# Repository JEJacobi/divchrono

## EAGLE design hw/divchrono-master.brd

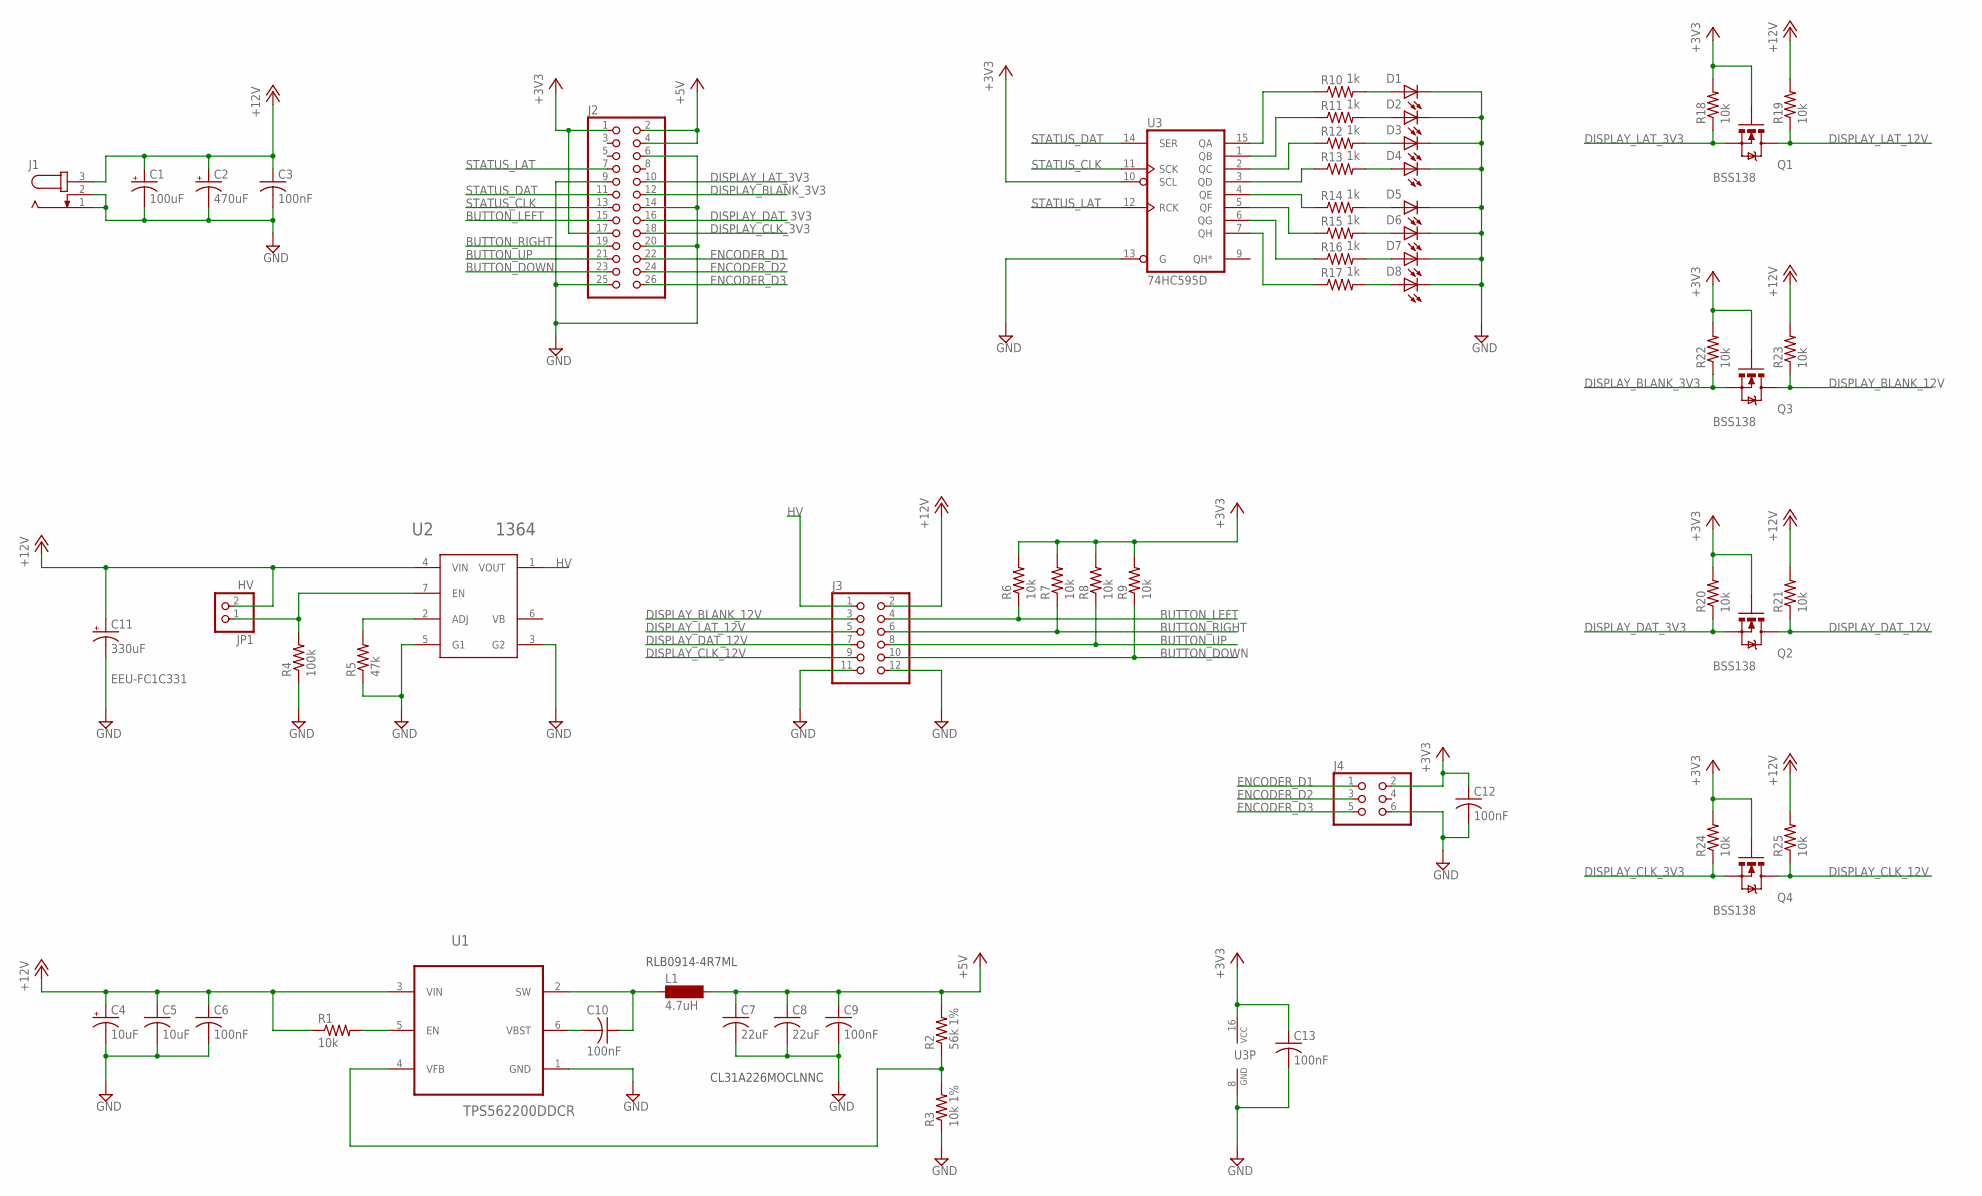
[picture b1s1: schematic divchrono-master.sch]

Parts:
C1: 100uF; E2,5-6
C2: 470uF; E2,5-6
C3, C6, C9, C10, C12, C13: 100nF; C1206
C4: 10uF; E2-5
C5: 10uF; C1206
C7, C8: 22uF; C1206
C11: 330uF; E3,5-8
D1, D2, D3, D4, D5, D6, D7, D8: LEDCHIPLED_1206; CHIPLED_1206
J1: JACK-PLUG0; SPC4077
J2: PINHD-2X13; 2X13
J3: PINHD-2X6; 2X06
J4: PINHD-2X3; 2X03
JP1: HV; 1X02
L1: 4.7uH; BS11
Q1, Q2, Q3, Q4: BSS138; SOT23-3
R1, R6, R7, R8, R9, R18, R19, R20, R21, R22, R23, R24, R25: 10k; R1206
R2: 56k 1%; R1206
R3: 10k 1%; R1206
R4: 100k; R1206
R5: 47k; R1206
R10, R11, R12, R13, R14, R15, R16, R17: 1k; R1206
U1: TPS562200DDCR; SOT95P280X110-6N
U2: 1364
U3: 74HC595D; SO16

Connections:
+3V3: C12.1, C13.1, J2.1, J2.17, J4.2, Q1.1 (G), Q2.1 (G), Q3.1 (G), Q4.1 (G), R6.2, R7.2, R8.2, R9.2, R18.2, R20.2, R22.2, R24.2, U3.10 (SCL), U3.16 (VCC)
+5V: C7.1, C8.1, C9.1, J2.2, J2.4, L1.2, R2.2
+12V: C1.+, C2.+, C3.1, C4.+, C5.1, C6.1, C11.+, J1.3, J3.2, JP1.2, R1.1, R19.2, R21.2, R23.2, R25.2, U1.3 (VIN), U2.4 (VIN)
BUTTON_DOWN: J2.23, J3.10, R9.1
BUTTON_LEFT: J2.15, J3.4, R6.1
BUTTON_RIGHT: J2.19, J3.6, R7.1
BUTTON_UP: J2.21, J3.8, R8.1
DISPLAY_BLANK_3V3: J2.12, Q3.2 (S), R22.1
DISPLAY_BLANK_12V: J3.3, Q3.3 (D), R23.1
DISPLAY_CLK_3V3: J2.18, Q4.2 (S), R24.1
DISPLAY_CLK_12V: J3.9, Q4.3 (D), R25.1
DISPLAY_DAT_3V3: J2.16, Q2.2 (S), R20.1
DISPLAY_DAT_12V: J3.7, Q2.3 (D), R21.1
DISPLAY_LAT_3V3: J2.10, Q1.2 (S), R18.1
DISPLAY_LAT_12V: J3.5, Q1.3 (D), R19.1
ENCODER_D1: J2.22, J4.1
ENCODER_D2: J2.24, J4.3
ENCODER_D3: J2.26, J4.5
GND: C1.-, C2.-, C3.2, C4.-, C5.2, C6.2, C7.2, C8.2, C9.2, C11.-, C12.2, C13.2, D1.C, D2.C, D3.C, D4.C, D5.C, D6.C, D7.C, D8.C, J1.1, J1.2, J2.6, J2.9, J2.14, J2.20, J2.25, J3.11, J3.12, J4.6, R3.1, R4.1, R5.1, U1.1 (GND), U2.3 (G2), U2.5 (G1), U3.8 (GND), U3.13 (G)
HV: J3.1, U2.1 (VOUT)
unnamed: R1.2, U1.5 (EN)
unnamed: C10.1, L1.1, U1.2 (SW)
unnamed: JP1.1, R4.2, U2.7 (EN)
unnamed: R5.2, U2.2 (ADJ)
unnamed: C10.2, U1.6 (VBST)
unnamed: R2.1, R3.2, U1.4 (VFB)
unnamed: R14.1, U3.4 (QE)
unnamed: R13.1, U3.3 (QD)
unnamed: R12.1, U3.2 (QC)
unnamed: D8.A, R17.2
unnamed: D7.A, R16.2
unnamed: D6.A, R15.2
unnamed: D5.A, R14.2
unnamed: R11.1, U3.1 (QB)
unnamed: R10.1, U3.15 (QA)
unnamed: R15.1, U3.5 (QF)
unnamed: R16.1, U3.6 (QG)
unnamed: R17.1, U3.7 (QH)
unnamed: D4.A, R13.2
unnamed: D3.A, R12.2
unnamed: D2.A, R11.2
unnamed: D1.A, R10.2
STATUS_CLK: J2.13, U3.11 (SCK)
STATUS_DAT: J2.11, U3.14 (SER)
STATUS_LAT: J2.7, U3.12 (RCK)

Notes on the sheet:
EEU-FC1C331
CL31A226MOCLNNC
RLB0914-4R7ML

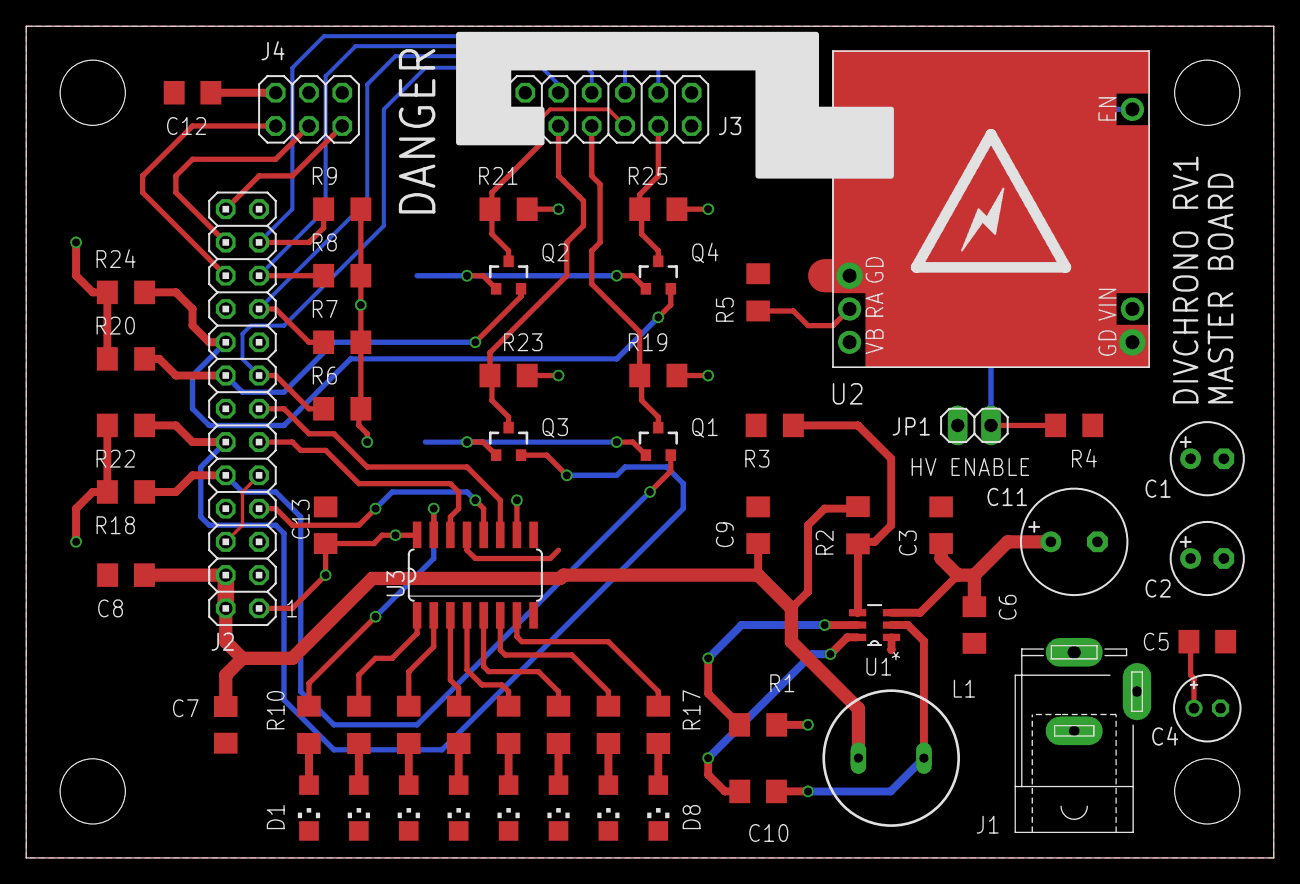
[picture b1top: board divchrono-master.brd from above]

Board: 2 copper layers, 95.2 x 63.5 mm, 61 parts (1 on the bottom side), 45 nets.

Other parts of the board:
U$1: ICON_DANGER
U$2: ICON_BOLT-L

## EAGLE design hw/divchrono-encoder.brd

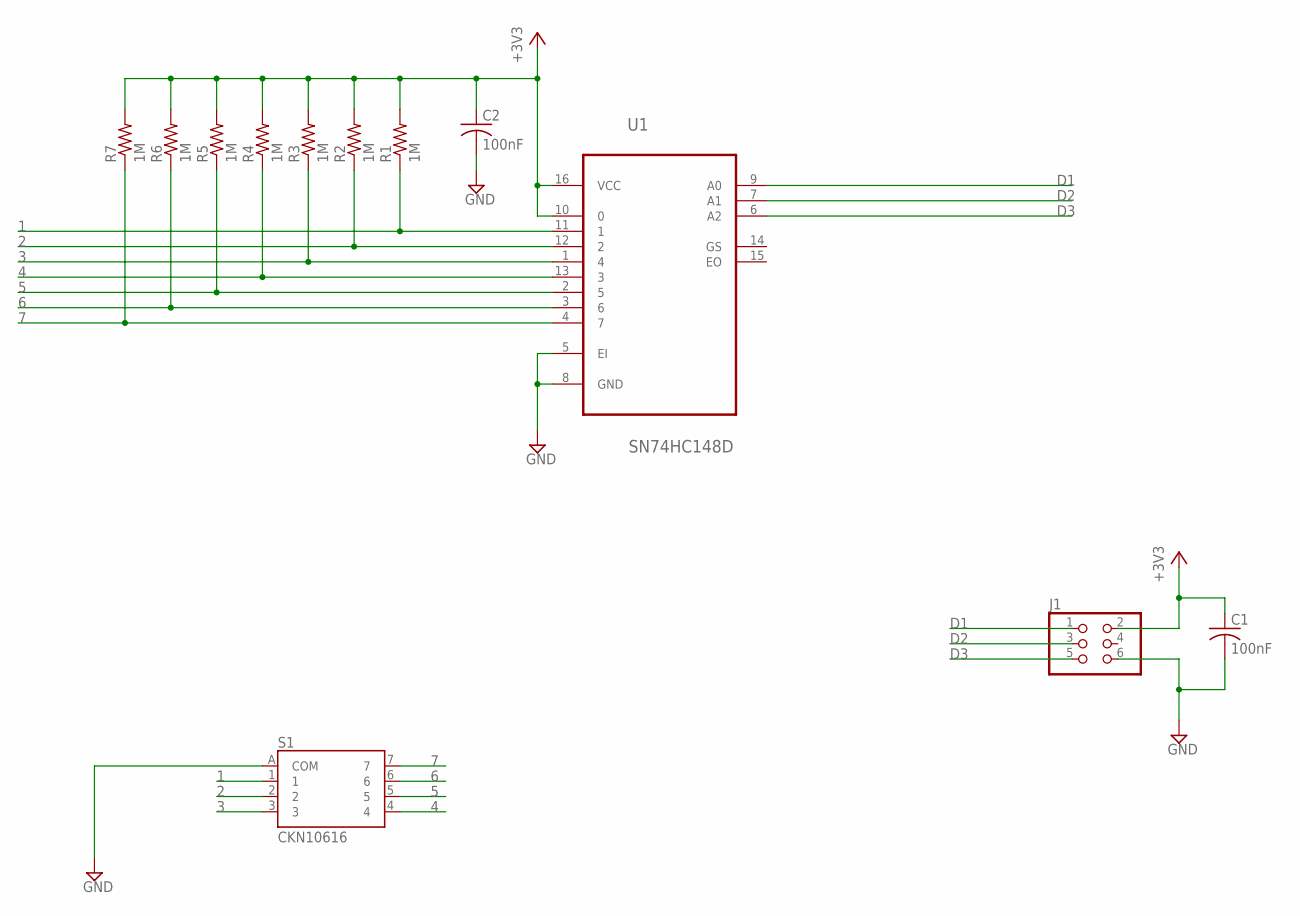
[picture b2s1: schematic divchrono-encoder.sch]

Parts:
C1, C2: 100nF; C1206
J1: PINHD-2X3; 2X03
R1, R2, R3, R4, R5, R6, R7: 1M; R1206
S1: CKN10616
U1: SN74HC148D; SOIC127P600X175-16N

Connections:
1: R1.1, S1.1, U1.11 (1)
2: R2.1, S1.2, U1.12 (2)
3: R3.1, S1.3, U1.1 (4)
4: R4.1, S1.4, U1.13 (3)
5: R5.1, S1.5, U1.2 (5)
6: R6.1, S1.6, U1.3 (6)
7: R7.1, S1.7, U1.4 (7)
+3V3: C1.1, C2.1, J1.2, R1.2, R2.2, R3.2, R4.2, R5.2, R6.2, R7.2, U1.10 (0), U1.16 (VCC)
D1: J1.1, U1.9 (A0)
D2: J1.3, U1.7 (A1)
D3: J1.5, U1.6 (A2)
GND: C1.2, C2.2, J1.6, S1.A (COM), U1.5 (EI), U1.8 (GND)

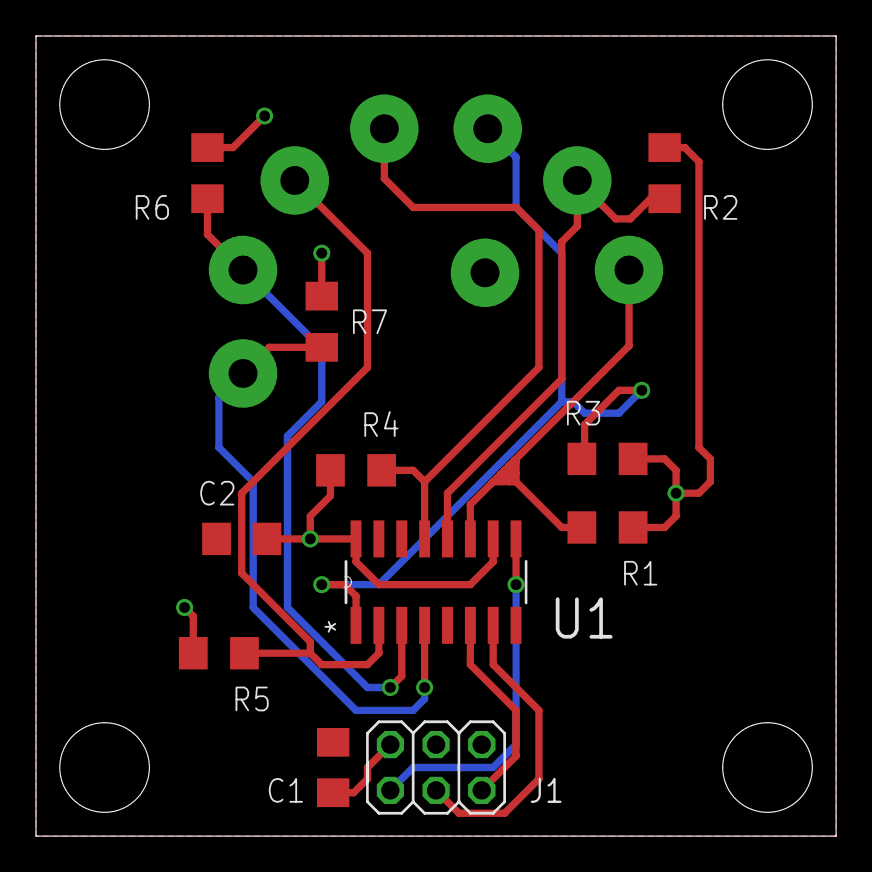
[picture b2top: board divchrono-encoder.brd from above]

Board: 2 copper layers, 44.5 x 44.5 mm, 12 parts (1 on the bottom side), 12 nets.

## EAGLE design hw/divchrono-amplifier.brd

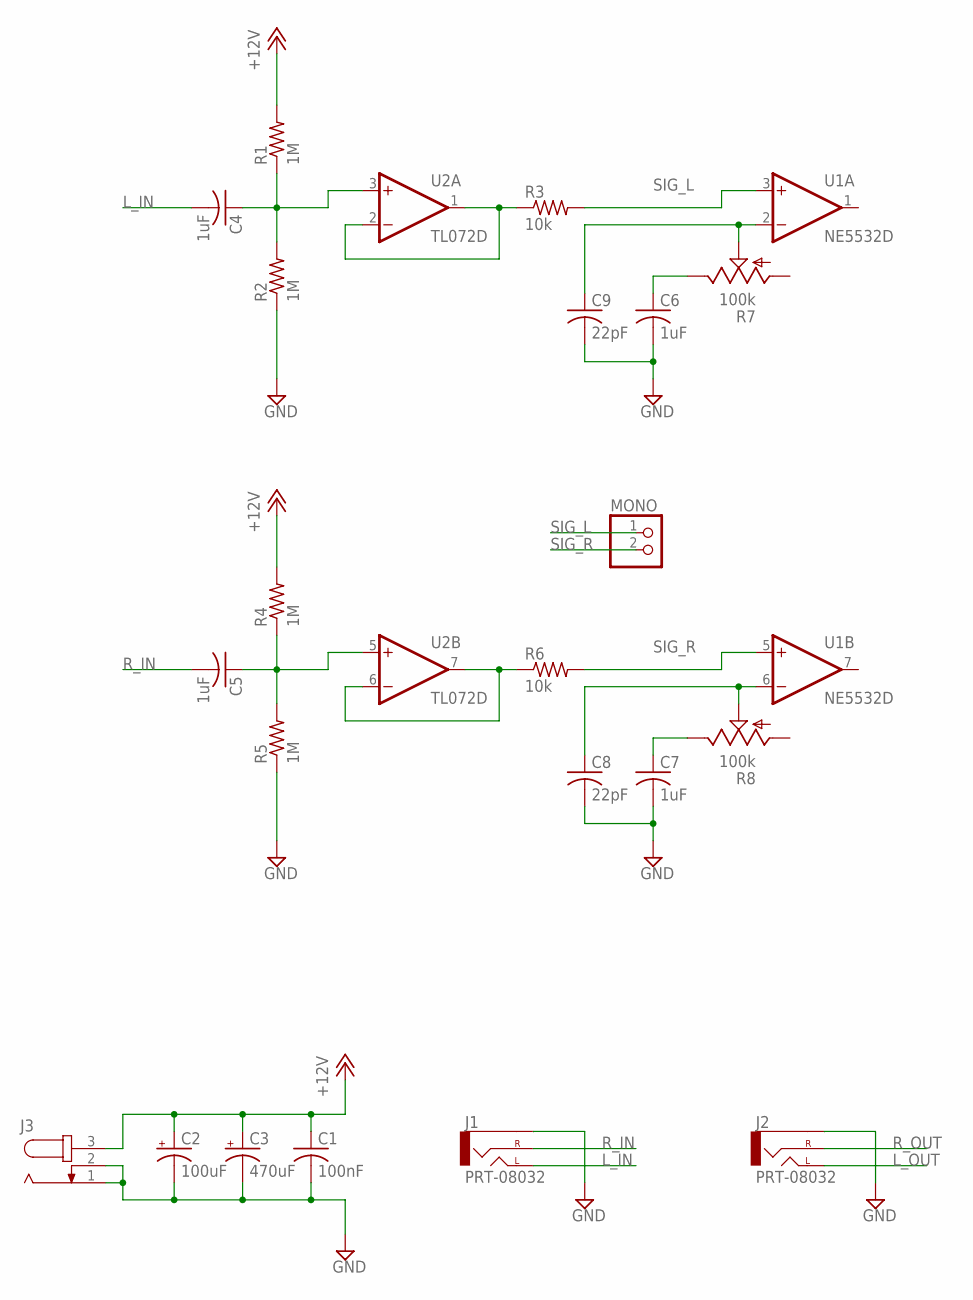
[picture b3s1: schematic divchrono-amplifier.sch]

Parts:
C1: 100nF; C1206
C2: 100uF; E2,5-6
C3: 470uF; E2,5-6
C4, C5, C6, C7: 1uF; C1206
C8, C9: 22pF; C1206
J1, J2: PRT-08032; AUDIO-JACK
J3: JACK-PLUG0; SPC4077
MONO: PINHD-1X2; 1X02
R1, R2, R4, R5: 1M; R1206
R3, R6: 10k; R1206
R7, R8: 100k; CT6
U1: NE5532D; SO08
U2: TL072D; SO08

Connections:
+12V: C1.1, C2.+, C3.+, J3.3, R1.2, R4.2
GND: C1.2, C2.-, C3.-, C6.2, C7.2, C8.2, C9.2, J1.SLEEVE, J2.SLEEVE, J3.1, J3.2, R2.1, R5.1
L_IN: C4.2, J1.TIP (LEFT)
L_OUT: J2.TIP (LEFT)
unnamed: C4.1, R1.1, R2.2, U2.3 (+IN)
unnamed: R3.1, U2.1 (OUT), U2.2 (-IN)
unnamed: C5.1, R4.1, R5.2, U2.5 (+IN)
unnamed: R6.1, U2.6 (-IN), U2.7 (OUT)
unnamed: C9.1, R7.S, U1.2 (-IN)
unnamed: C8.1, R8.S, U1.6 (-IN)
unnamed: C6.1, R7.E
unnamed: C7.1, R8.E
R_IN: C5.2, J1.RING (RIGHT)
R_OUT: J2.RING (RIGHT)
SIG_L: MONO.1, R3.2, U1.3 (+IN)
SIG_R: MONO.2, R6.2, U1.5 (+IN)
V+: U1.8 (V+), U2.8 (V+)
V-: U1.4 (V-), U2.4 (V-)

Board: 2 copper layers, 23 parts (0 on the bottom side), 16 nets, no tracks yet.

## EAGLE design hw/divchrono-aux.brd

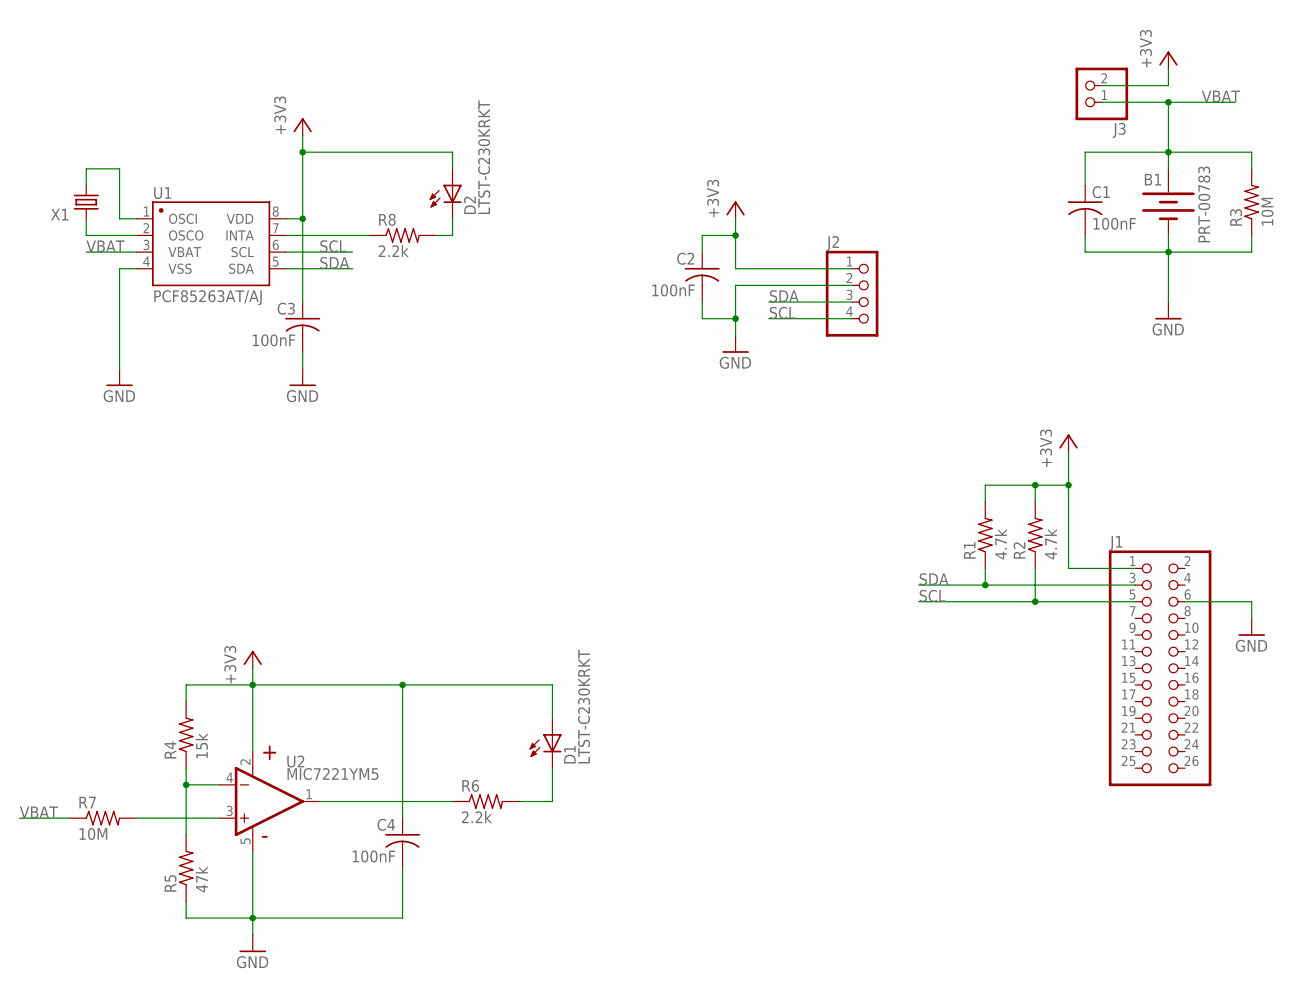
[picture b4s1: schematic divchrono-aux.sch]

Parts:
B1: PRT-00783; BATTCOM_20MM_PTH
C1, C2, C3, C4: 100nF; C1206
D1, D2: LTST-C230KRKT; CHIPLED_1206
J1: PINHD-2X13; 2X13
J2: PINHD-1X4; 1X04
J3: PINHD-1X2; 1X02
R1, R2: 4.7k; R1206
R3, R7: 10M; R1206
R4: 15k; R1206
R5: 47k; R1206
R6, R8: 2.2k; R1206
U1: PCF85263AT/AJ; SOIC-8
U2: MIC7221YM5; SOT23-5
X1: CRYSTALS-NOGND-WATCH-3X8; WATCH-3X8

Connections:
+3V3: C2.1, C3.1, C4.1, D1.A, D2.A, J1.1, J2.1, J3.2, R1.2, R2.2, R4.2, U1.8 (VDD), U2.2 (V+)
GND: B1.2 (-), C1.2, C2.2, C3.2, C4.2, J1.6, J2.2, R3.1, R5.1, U1.4 (VSS), U2.5 (V-)
unnamed: R6.1, U2.1 (OUT)
unnamed: R4.1, R5.2, U2.4 (-IN)
unnamed: D1.C, R6.2
unnamed: U1.2 (OSCO), X1.1
unnamed: U1.1 (OSCI), X1.2
unnamed: R7.2, U2.3 (+IN)
unnamed: D2.C, R8.2
unnamed: R8.1, U1.7 (INTA)
SCL: J1.5, J2.4, R2.1, U1.6 (SCL)
SDA: J1.3, J2.3, R1.1, U1.5 (SDA)
VBAT: B1.1 (+), C1.1, J3.1, R3.2, R7.1, U1.3 (VBAT)

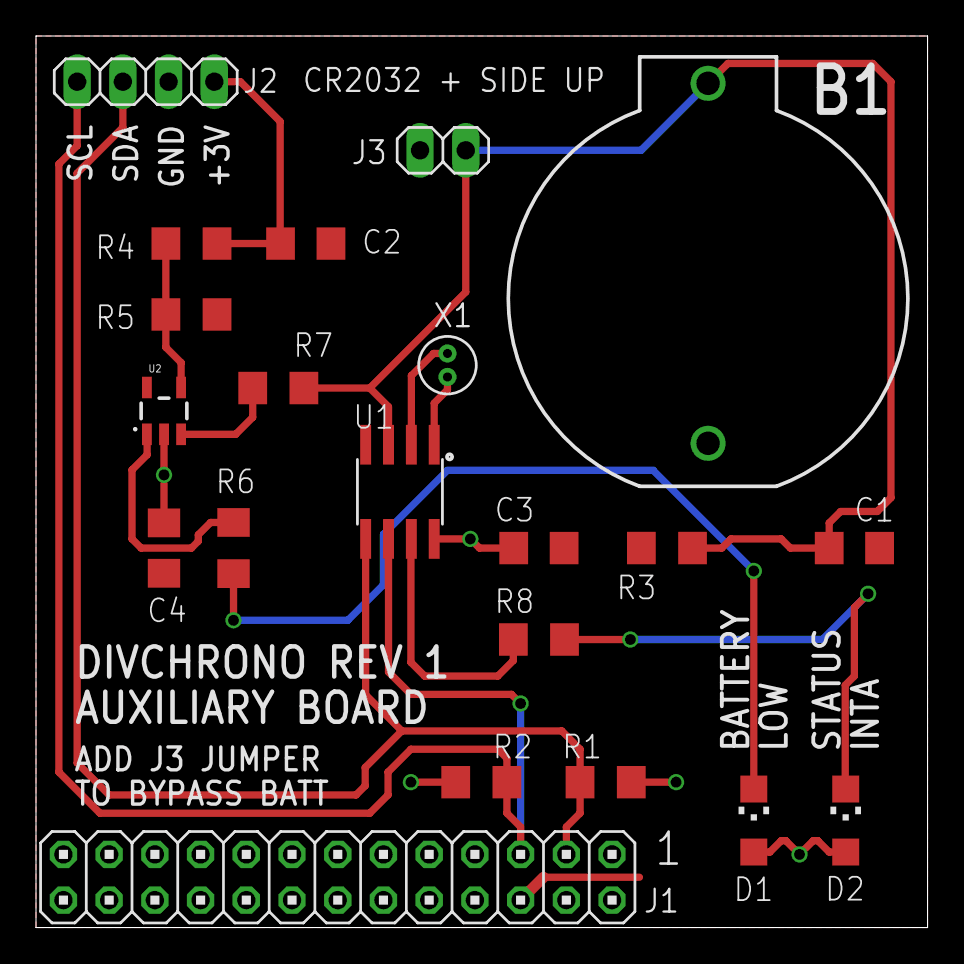
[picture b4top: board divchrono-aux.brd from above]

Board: 2 copper layers, 49.5 x 49.5 mm, 21 parts (0 on the bottom side), 13 nets.

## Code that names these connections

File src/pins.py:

"""
Module for handling GPIO pin setup and settings.

Uses RPi.GPIO
"""

import RPi.GPIO as GPIO

mode = GPIO.BCM    # GPIO addressing system. Use the BCM ports instead of IO numbers.

status_data = 17   # For status LED shift register.
status_clock = 27
status_latch = 4
display_data = 23  # For Nixie tube shift registers.
display_clock = 24
display_latch = 15
display_blank = 18 # Nixie tube PWM brightness control.

button_left = 22   # Case pushbuttons (active low).
button_right = 10
button_up = 9
button_down = 11
encoder_d1 = 25    # Encoded rotary switch data.
encoder_d2 = 8
encoder_d3 = 7

# Pins to configure as outputs:

outputs = [
    status_data, 
    status_clock, 
    status_latch, 
    display_data,
    display_clock,
    display_latch,
    display_blank
]

# Pins to configure as inputs:

inputs = [
    button_left,
    button_right,
    button_up,
    button_down,
    encoder_d1,
    encoder_d2,
    encoder_d3
]

def init():
    """Initalize GPIO, set up input and output pins."""

    # TODO: Log any warnings and raspi board information with GPIO.RPI_INFO.
    #       Also report current GPIO module version with GPIO.VERSION.

    GPIO.setwarnings(False)
    GPIO.setmode(mode)
    GPIO.setup(inputs, GPIO.IN)
    GPIO.setup(outputs, GPIO.OUT, initial=GPIO.LOW)

def destroy():
    """Clean up, stop using GPIO pins."""
    GPIO.cleanup()

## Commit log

2016-09-26 Initial commit, includes completed auxiliary board and partial master board, as well as placeholder software and audio folder.
2016-09-27 Adds GPIO settings and status light shift register control.
2016-10-03 Documentation update, added information on external amplifier, master board, and fixed some typos.
2016-10-03 Added Nixie tube boost converter into schematic, library, and updated documentation for new layout.
2016-10-04 Added some pin mapping documentation and updated other files.
2016-10-04 Mirrored pin mappings onto schematic, and fixed two small documentation errors.
2016-10-05 Relocates GPIO initalization and cleanup to pins.py.
2016-10-05 Configures pins.py properly.
2016-10-05 Laid out major board connections/pin mappings, and started on framework for encoder and amplifier boards. Minor documentation updates to reflect changes.
2016-10-05 Minor cleanup, added comments, and fixed style.
2016-10-06 Finished display interface and started master board schematic finalization.
2016-10-14 Updated encoder board and documentation for new design using a SN74HC148 encoder instead of a custom PIC.
2016-10-16 Finished initial encoder board schematic and layout. Checked ERC/DRC, updated documentation, and compiled gerbers.
2016-10-17 Started on automated install script and some minor documentation updates.
2016-10-17 Fixed silkscreen fonts, changed from proportional to vector and rebuilt gerbers.
2016-10-18 Updated BOM with encoder board parts list.
2016-10-20 Final modifications before master board layout. Changed status LED hookup to allow more streamlined part positioning.
2016-10-20 Added master board partslist to BOM.
2016-10-24 Finished initial layout for master board, minor schematic and BOM changes.
2016-10-24 Made gerber build of master board, added library for warnings, and cleaned up library files into folder.
2016-11-08 Added PDF versions of schematics.
2016-11-24 Added encoder module and whipped up a quick test for status/encoder routines.
2016-11-24 Updated encoder documentation with new mappings.
2016-11-29 Added main daemon/signal loop, added cleanup functions for pins and status display, general documentation cleanup.
2016-11-30 Added audio file for testing.

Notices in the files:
parts and their libraries:
SparkFun-Connectors: Licensing: Creative Commons ShareAlike 4.0 International - https://creativecommons.org/licenses/by-sa/4.0
dicons: Copyright (C) 2004, Bob Starr (rtzaudio@mindspring.com)
